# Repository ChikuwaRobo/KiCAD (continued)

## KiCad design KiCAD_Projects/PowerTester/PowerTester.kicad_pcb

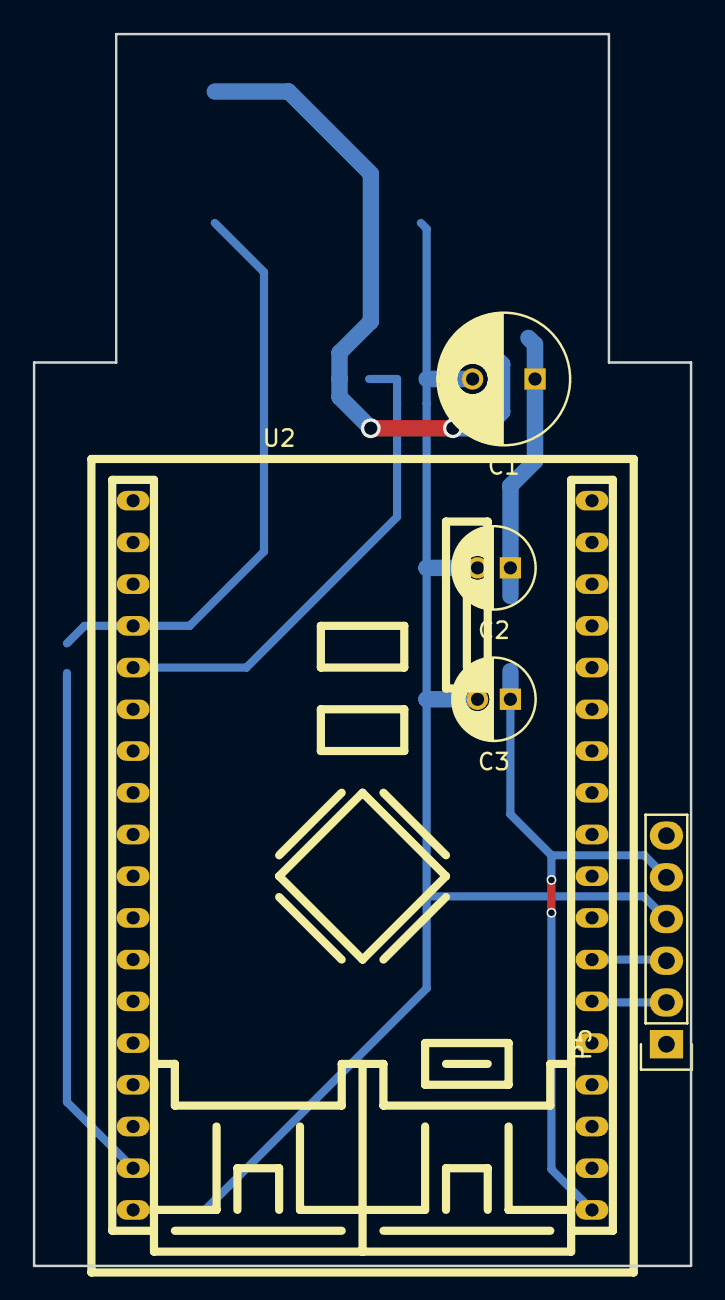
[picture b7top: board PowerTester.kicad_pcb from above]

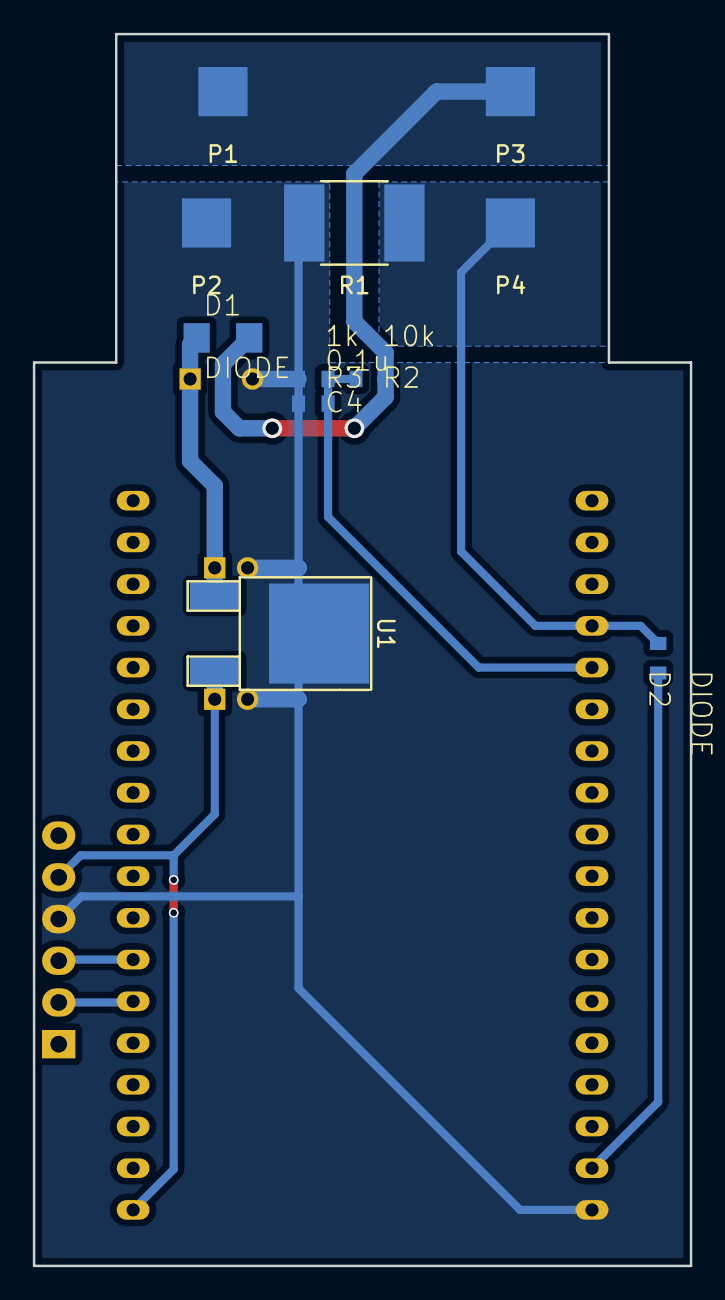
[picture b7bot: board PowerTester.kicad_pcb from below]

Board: 2 copper layers, 40.0 x 75.0 mm, 16 parts (11 on the bottom side), 9 nets.

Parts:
C1: 100u; C_Radial_D8_L13_P3.8
C2, C3: 10u; C_Radial_D5_L11_P2
C4: 0.1u; C1608_WP
D1: DIODE; C3216
D2: DIODE; C1608_WP
P1, P2, P3, P4: CONN_01X01; Measurement_Point_Square-SMD-Pad_Big
P5: CONN_01X06; Socket_Strip_Straight_1x06
R1: 1m; R_2816
R2: 10k; C1608_WP
R3: 1k; C1608_WP
U1: LM7812; TO-252-2Lead_regu
U2: F103_mini

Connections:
+5V: C3.1, P5.5, U1.VO, U2.19
+BATT: D1.2, P1.1, P3.1, R2.1
/Isense: D2.2, P4.1, R1.1, U2.4
/RX: P5.3, U2.25
/TX: P5.2, U2.24
/Vsense: C4.1, R2.2, R3.1, U2.5
GND: C1.2, C2.2, C3.2, C4.2, P2.1, P5.4, R1.2, R3.2, U1.GND, U2.18
unnamed: C1.1, C2.1, D1.1, U1.VI
unnamed: D2.1, U2.17
